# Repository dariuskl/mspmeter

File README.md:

# MSPmeter

This is an ongoing development for a flexible voltage & current meter based on
MSP430i2x, currently in somewhat of a proof-of-concept phase. The goal is to
have a template that can be easily adapted to replace analog or inaccurate
digital panel meters in existing power supplies or to integrate into new
designs. Accuracy-wise it would be nice to achieve .1 mV resp. .1 mA, so that
the readout can be trusted at a resolution of 1 mV resp. 1 mA.

## Planned features

- Buzzer
- Persistent calibration

## User manual

### Digital readout & indicators

### Heartbeat LED

### Buzzer

### Serial interface

9600N1

### Calibration & configuration

# Hardware

## Design notes

### Achievable accuracy

The required accuracy is 1 mV maximum error for the voltage measurement (because
we are aiming for a resolution of 10 mV) and 0.1 mA maximum error for the
current measurement (again, because we are aiming for a resolution of 1 mA).

The internal measurement circuitry of the power supply sources 1 mA for
full-scale voltage and current. To obtain 928 mV max. full-scale ADC input,
a resistor is used to drop a proportional voltage.

    R = 928 mV / 1 mA = 928 Ω

The next closest standard value *below* (we do not want to exceed that voltage)
is 910 Ω. The best readily available performer is `RN73H1JTTD9100A05` with 0.05%
tolerance and 5ppm/°C temperature drift.

That configuration yields below voltage input specification to the ADC.

    0..1 mA / (910 R ± 0.05% ± 5ppm/°C) = 910 mV ± 0.05% ± 5ppm/°C

An operating temperature range of 15 to 60 °C is a reasonable choice for such an
instrument. This yields a worst-case error range of

    0.910 * 0.000005 * (15 - 25) = −0,0000455 (~0,05 mV)
    0.910 * 0.000005 * (60 - 25) =  0,00015925 (~0,16 mV)

The final accuracy specification based on the input circuit over the full
temperature range is thus ~ 5 mV error (in terms of measured output voltage)
and ~ 0.2 mA error (in terms of measured output current).

## I/O

    ──────────────┐
             P1.0 ├─ HEARTBEAT
             P1.1 ├─
     UCA0RXD/P1.2 ├─ Rx
     UCA0TXD/P1.3 ├─ Tx
     UCB0STE/P1.4 ├─ RCLK
     UCB0CLK/P1.5 ├─ SRCLK
       TA0.2/P1.6 ├─ BUZZER
    UCB0SIMO/P1.7 ├─ SER
                  │
             P2.0 ├─ nS1_PRESSED
             P2.1 ├─ ENCODER_A
             P2.2 ├─ ENCODER_B
             P2.3 ├─
    ──────────────┘

## Adjustment procedure

A correctly adjusted unit can achieve accuracy of ???

| Parameter | VCC | Min | Typ | Max | Unit |
|-----------|-----|-----|-----|-----|------|
| VREF      | 3 V | 1.0 | 1.2 | 1.5 | V    |
| ZID       | 3 V | 300 | 400 |     | kΩ   |

The adjustment steps have to performed in the exact order in which they are
given here and no steps may be skipped. There is no way to cancel the adjustment
half-way through.

### Input attenuator trim

If the input attenuator consists of fixed resistors, this step will be skipped.
It is not advisable to use a trimmer due to the associated temperature
coefficient, which is usually much higher than in good fixed resistors.

The input attenuator must be adjusted such that a nominal full-scale input 
yields a voltage of 928 mV on the input pins. In the range of ±928 mV is where
the MSP has the best accuracy (at a gain of 1). Otherwise, the setting is not
critical for accuracy. Just make sure not to exceed 928 mV with the range of
interest. In case of doubt, choose an input voltage in excess of the range.

1. Connect an external voltage source of the nominal full-scale input voltage to
     the input;
2. connect a voltmeter directly to the analog inputs of the MSP; then
3. adjust the trimmer for a reading of 928 mV.

### Voltage reference

To calibrate the voltage reference

1. connect a precise (how precise?) external voltage (what value?) to any (which?) input (how can I measure just the external voltage without the input circuit?);
2. measure the applied input voltage,
3. calculate actual reference voltage from theoretical value
4. check plausibility
5. apply

### Input dividers, impedance, & offset

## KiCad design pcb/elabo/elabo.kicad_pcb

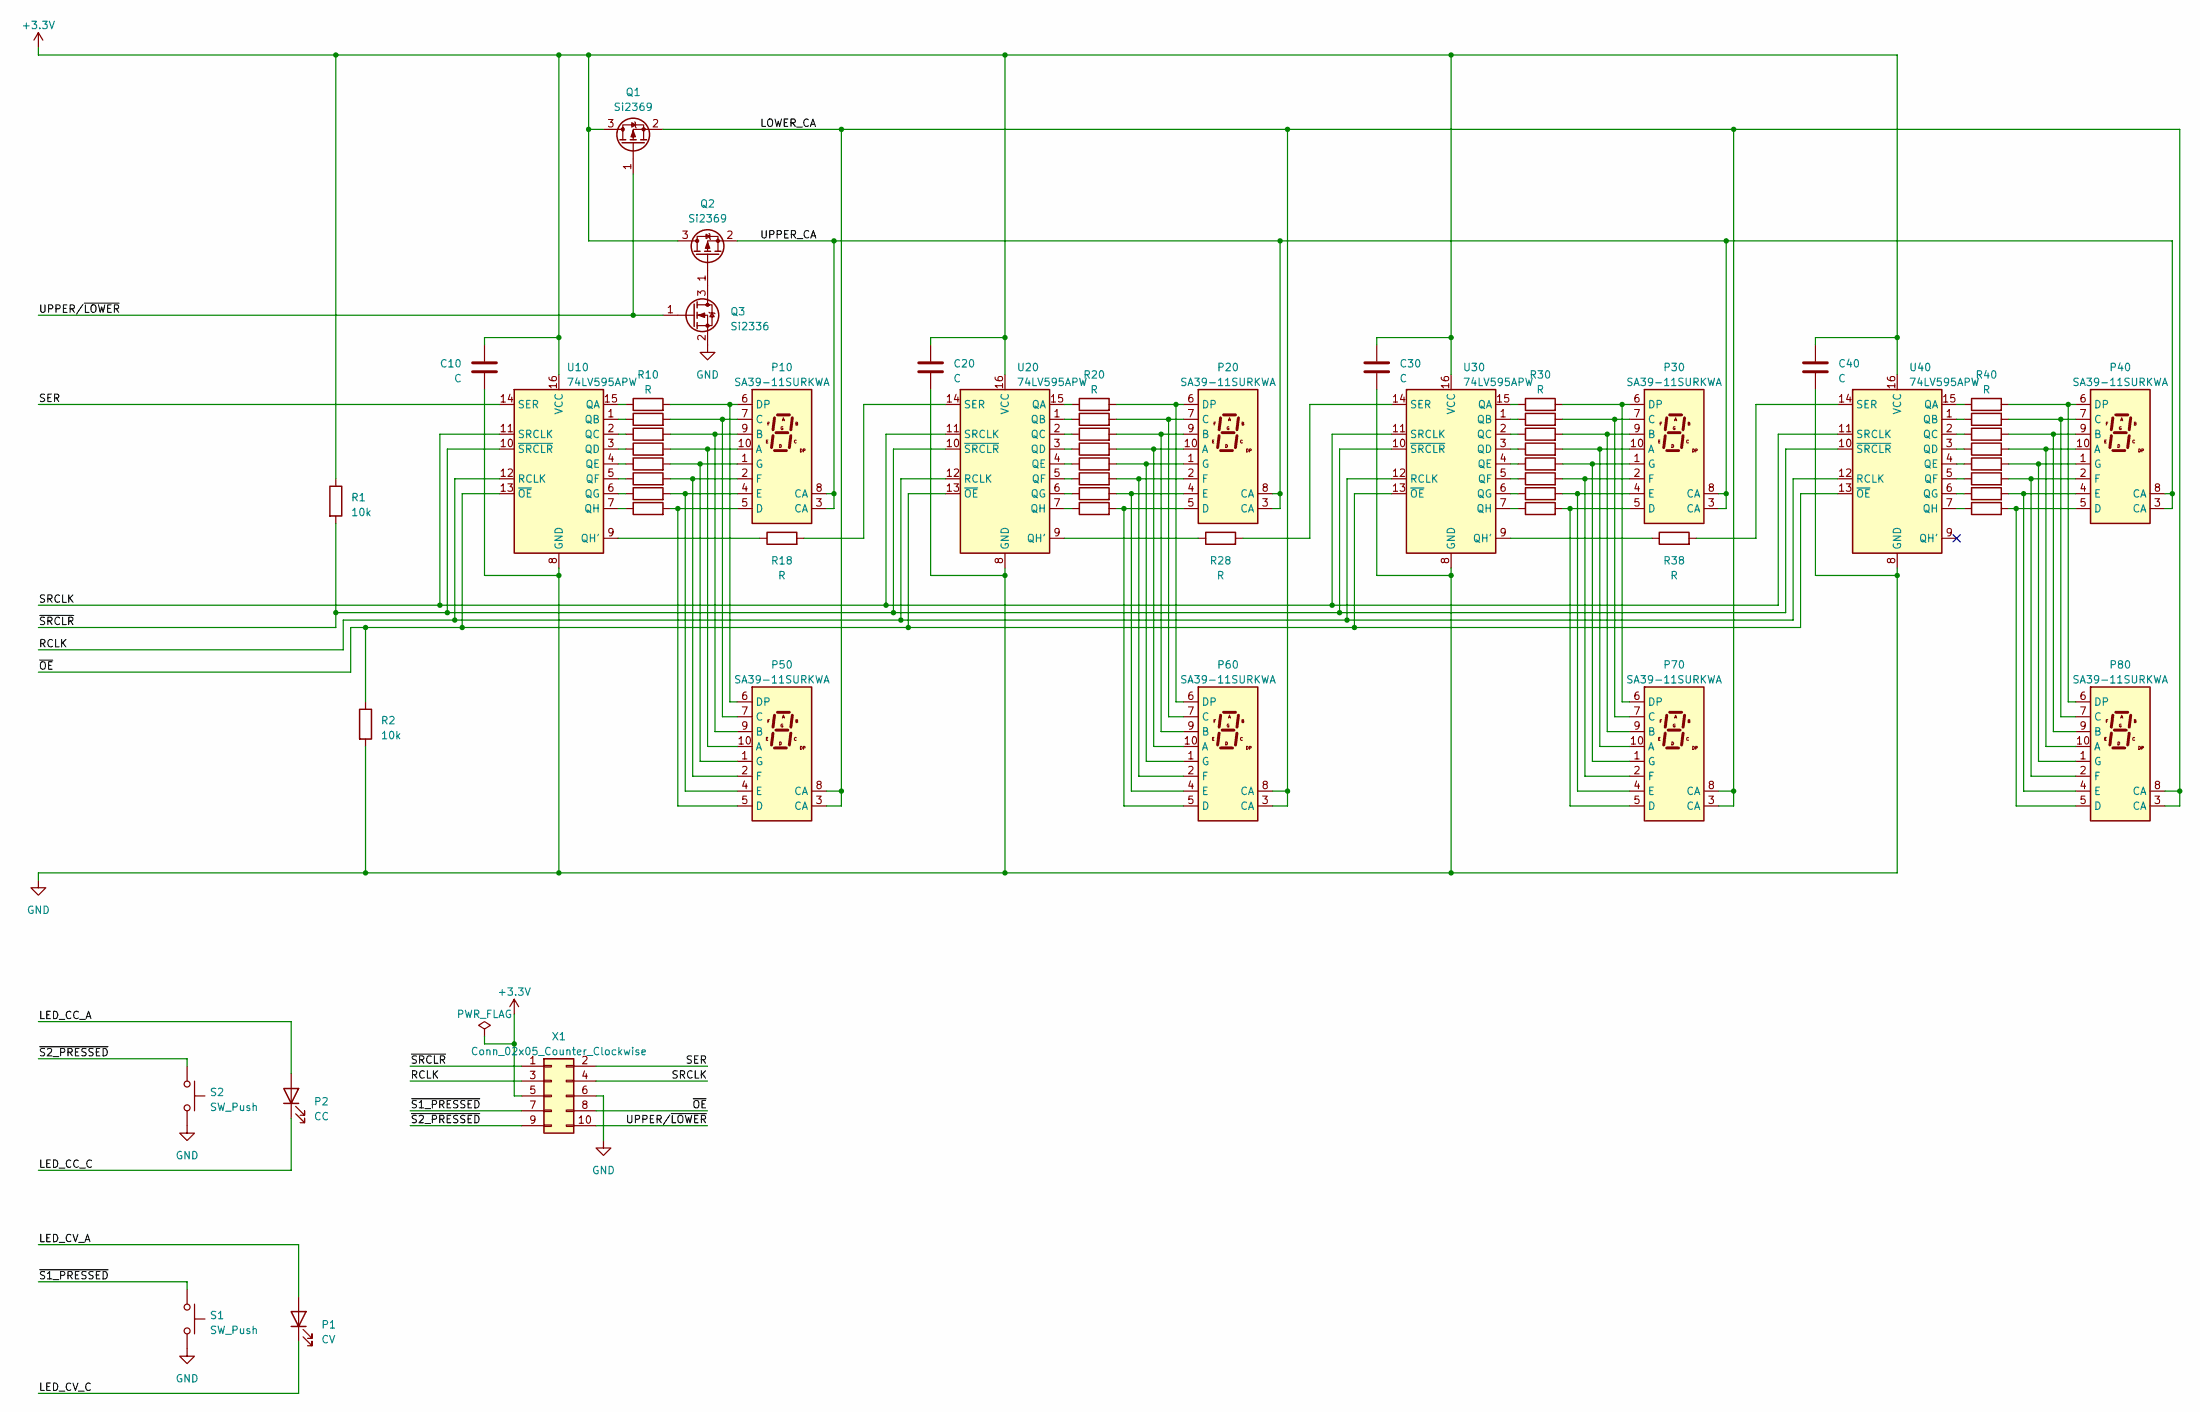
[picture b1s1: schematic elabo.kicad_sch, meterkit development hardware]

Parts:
C10, C20, C30, C40: C; C_0603_1608Metric
P1: CV; LED_D3.0mm_FlatTop
P2: CC; LED_D3.0mm_FlatTop
P10, P20, P30, P40, P50, P60, P70, P80: SA39-11SURKWA; Sx39-1xxxxx
Q1, Q2: Si2369; SOT-23-3
Q3: Si2336; SOT-23-3
R1, R2: 10k; R_0603_1608Metric
R10, R11, R12, R13, R14, R15, R16, R17, R18, R20, R21, R22, R23, R24, R25, R26, R27, R28, R30, R31, R32, R33, R34, R35, R36, R37, R38, R40, R41, R42, R43, R44, R45, R46, R47: R; R_0603_1608Metric
S1, S2: SW_Push; SW_PUSH_6mm_H13mm
U10, U20, U30, U40: 74LV595APW; TSSOP-16_4.4x5mm_P0.65mm
X1: Conn_02x05_Counter_Clockwise; PinHeader_2x05_P2.54mm_Vertical

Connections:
+3.3V: C10.1, C20.1, C30.1, C40.1, Q1.3 (D), Q2.3 (D), R1.1, U10.16 (VCC), U20.16 (VCC), U30.16 (VCC), U40.16 (VCC), X1.5
/LED_CC_A: P2.2 (A)
/LED_CC_C: P2.1 (K)
/LED_CV_A: P1.2 (A)
/LED_CV_C: P1.1 (K)
/LOWER_CA: P50.3 (CA), P50.8 (CA), P60.3 (CA), P60.8 (CA), P70.3 (CA), P70.8 (CA), P80.3 (CA), P80.8 (CA), Q1.2 (S)
/RCLK: U10.12 (RCLK), U20.12 (RCLK), U30.12 (RCLK), U40.12 (RCLK), X1.3
/SER: U10.14 (SER), X1.2
/SRCLK: U10.11 (SRCLK), U20.11 (SRCLK), U30.11 (SRCLK), U40.11 (SRCLK), X1.4
/UPPER_CA: P10.3 (CA), P10.8 (CA), P20.3 (CA), P20.8 (CA), P30.3 (CA), P30.8 (CA), P40.3 (CA), P40.8 (CA), Q2.2 (S)
/UPPER/~LOWER: Q1.1 (G), Q3.1 (G), X1.10
/~OE: R2.1, U10.13 (~OE), U20.13 (~OE), U30.13 (~OE), U40.13 (~OE), X1.8
/~S1_PRESSED: S1.1, X1.7
/~S2_PRESSED: S2.1, X1.9
/~SRCLR: R1.2, U10.10 (~SRCLR), U20.10 (~SRCLR), U30.10 (~SRCLR), U40.10 (~SRCLR), X1.1
GND: C10.2, C20.2, C30.2, C40.2, Q3.2 (S), R2.2, S1.2, S2.2, U10.8 (GND), U20.8 (GND), U30.8 (GND), U40.8 (GND), X1.6
unnamed: P10.10 (A), P50.10 (A), R13.2
unnamed: P10.9 (B), P50.9 (B), R12.2
unnamed: P10.7 (C), P50.7 (C), R11.2
unnamed: P10.5 (D), P50.5 (D), R17.2
unnamed: P10.6 (DP), P50.6 (DP), R10.2
unnamed: P10.4 (E), P50.4 (E), R16.2
unnamed: P10.2 (F), P50.2 (F), R15.2
unnamed: P10.1 (G), P50.1 (G), R14.2
unnamed: P20.10 (A), P60.10 (A), R23.2
unnamed: P20.9 (B), P60.9 (B), R22.2
unnamed: P20.7 (C), P60.7 (C), R21.2
unnamed: P20.5 (D), P60.5 (D), R27.2
unnamed: P20.6 (DP), P60.6 (DP), R20.2
unnamed: P20.4 (E), P60.4 (E), R26.2
unnamed: P20.2 (F), P60.2 (F), R25.2
unnamed: P20.1 (G), P60.1 (G), R24.2
unnamed: P30.10 (A), P70.10 (A), R33.2
unnamed: P30.9 (B), P70.9 (B), R32.2
unnamed: P30.7 (C), P70.7 (C), R31.2
unnamed: P30.5 (D), P70.5 (D), R37.2
unnamed: P30.6 (DP), P70.6 (DP), R30.2
unnamed: P30.4 (E), P70.4 (E), R36.2
unnamed: P30.2 (F), P70.2 (F), R35.2
unnamed: P30.1 (G), P70.1 (G), R34.2
unnamed: P40.10 (A), P80.10 (A), R43.2
unnamed: P40.9 (B), P80.9 (B), R42.2
unnamed: P40.7 (C), P80.7 (C), R41.2
unnamed: P40.5 (D), P80.5 (D), R47.2
unnamed: P40.6 (DP), P80.6 (DP), R40.2
unnamed: P40.4 (E), P80.4 (E), R46.2
unnamed: P40.2 (F), P80.2 (F), R45.2
unnamed: P40.1 (G), P80.1 (G), R44.2
unnamed: Q2.1 (G), Q3.3 (D)
unnamed: R10.1, U10.15 (QA)
unnamed: R11.1, U10.1 (QB)
unnamed: R12.1, U10.2 (QC)
unnamed: R13.1, U10.3 (QD)
unnamed: R14.1, U10.4 (QE)
unnamed: R15.1, U10.5 (QF)
unnamed: R16.1, U10.6 (QG)
unnamed: R18.1, U10.9 (QH')
unnamed: R17.1, U10.7 (QH)
unnamed: R20.1, U20.15 (QA)
unnamed: R21.1, U20.1 (QB)
unnamed: R22.1, U20.2 (QC)
unnamed: R23.1, U20.3 (QD)
unnamed: R24.1, U20.4 (QE)
unnamed: R25.1, U20.5 (QF)
unnamed: R26.1, U20.6 (QG)
unnamed: R28.1, U20.9 (QH')
unnamed: R27.1, U20.7 (QH)
unnamed: R18.2, U20.14 (SER)
unnamed: R30.1, U30.15 (QA)
unnamed: R31.1, U30.1 (QB)
unnamed: R32.1, U30.2 (QC)
unnamed: R33.1, U30.3 (QD)
unnamed: R34.1, U30.4 (QE)
unnamed: R35.1, U30.5 (QF)
unnamed: R36.1, U30.6 (QG)
unnamed: R38.1, U30.9 (QH')
unnamed: R37.1, U30.7 (QH)
unnamed: R28.2, U30.14 (SER)
unnamed: R40.1, U40.15 (QA)
unnamed: R41.1, U40.1 (QB)
unnamed: R42.1, U40.2 (QC)
unnamed: R43.1, U40.3 (QD)
unnamed: R44.1, U40.4 (QE)
unnamed: R45.1, U40.5 (QF)
unnamed: R46.1, U40.6 (QG)
unnamed: R47.1, U40.7 (QH)
unnamed: R38.2, U40.14 (SER)

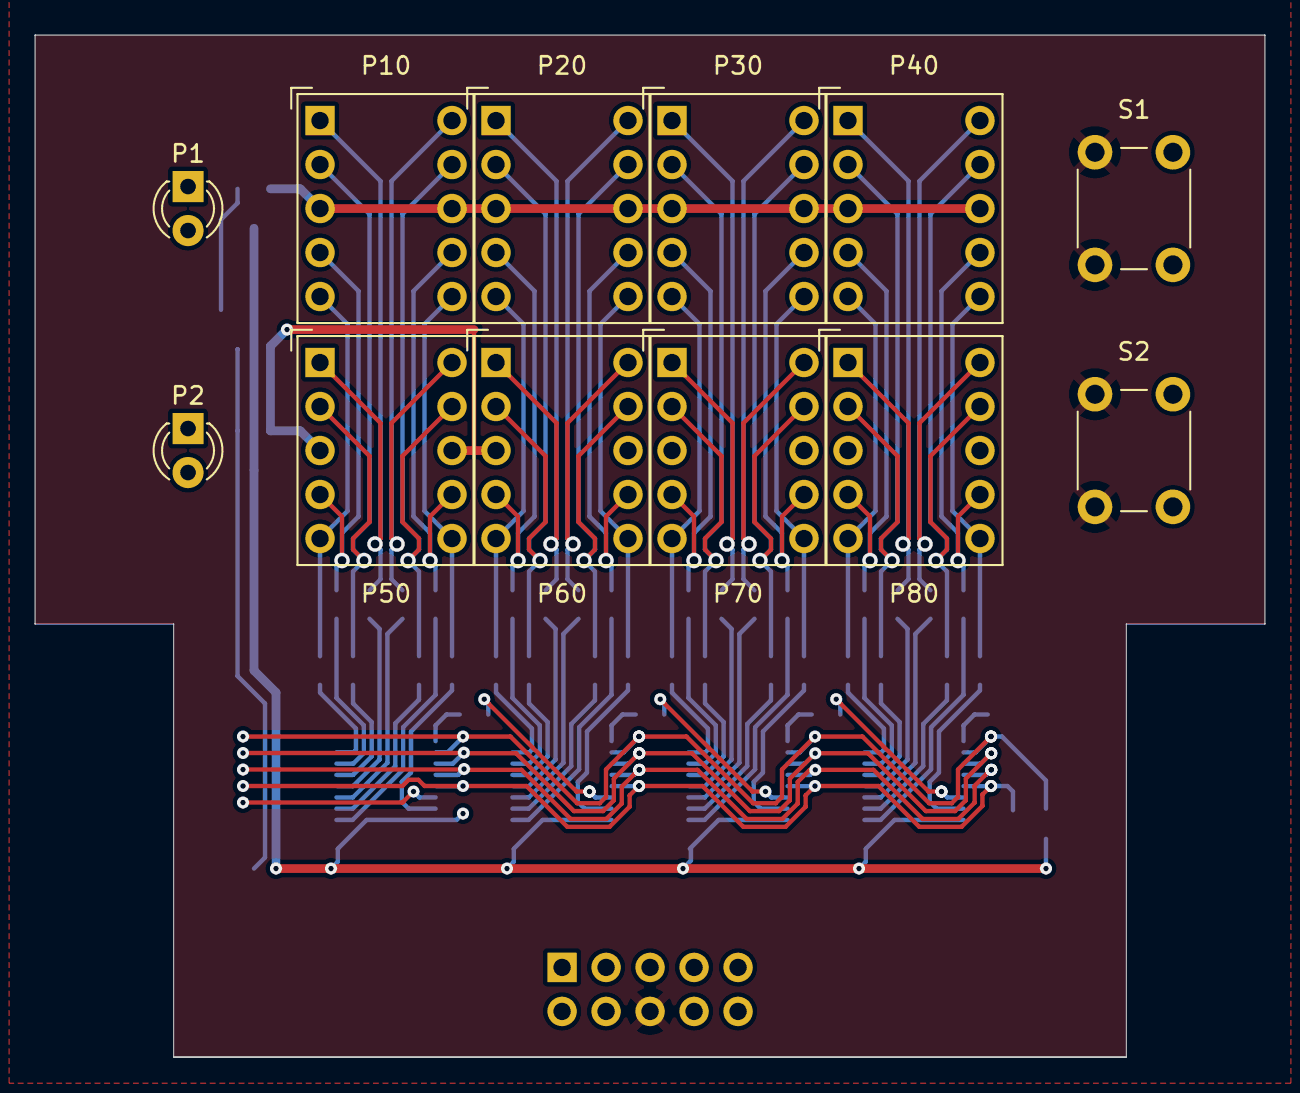
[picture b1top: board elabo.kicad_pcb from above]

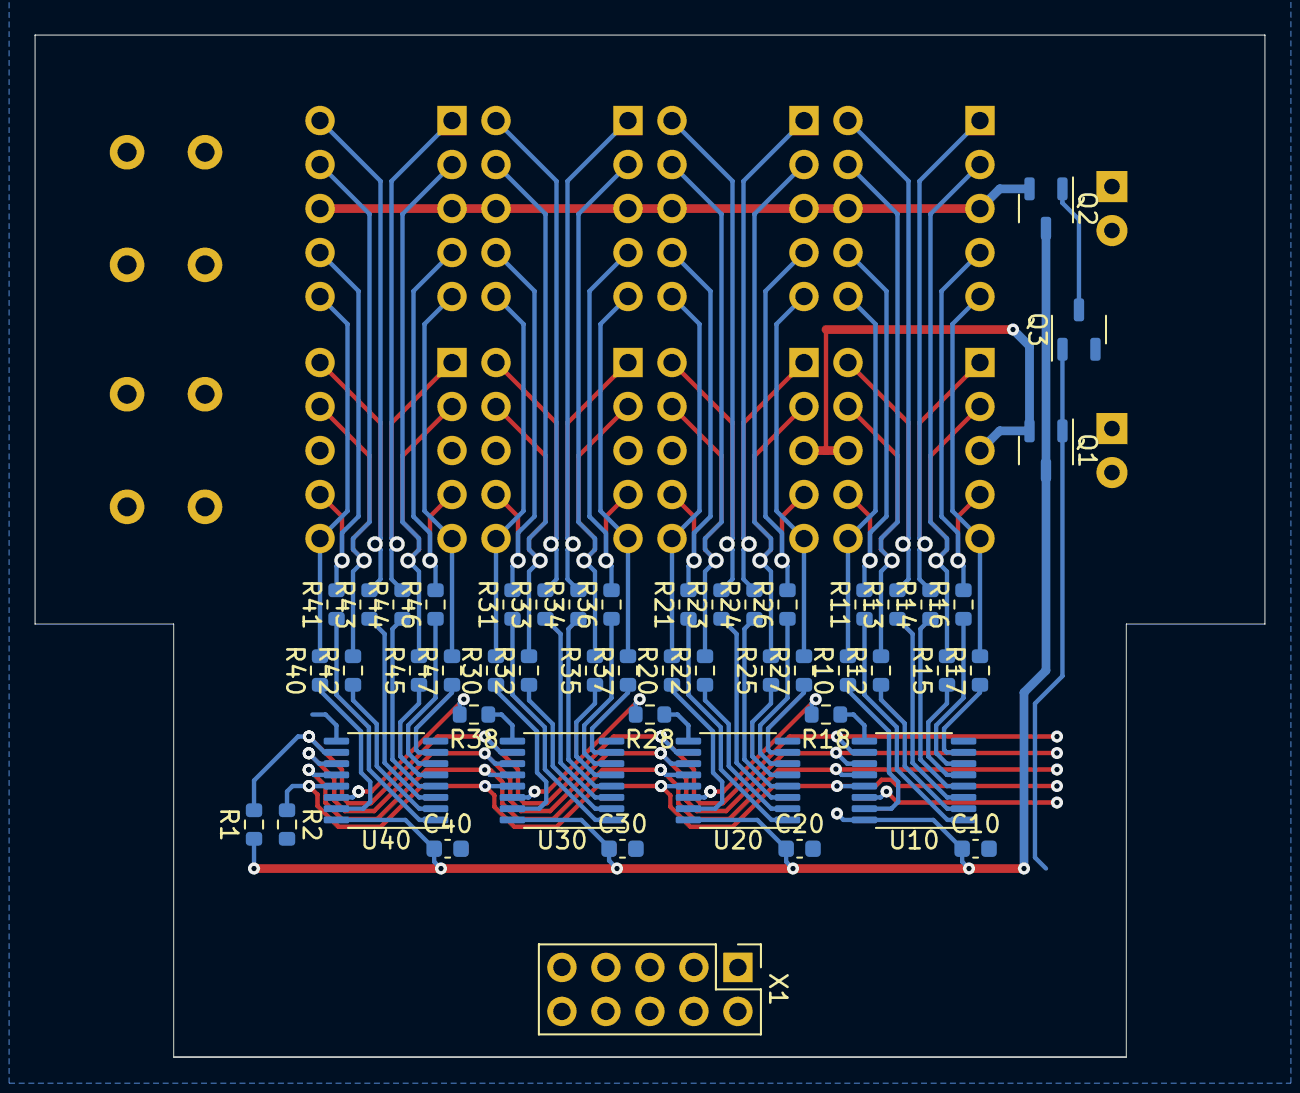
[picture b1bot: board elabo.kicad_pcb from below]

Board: 2 copper layers, 71.0 x 59.0 mm, 61 parts (49 on the bottom side), 83 nets.

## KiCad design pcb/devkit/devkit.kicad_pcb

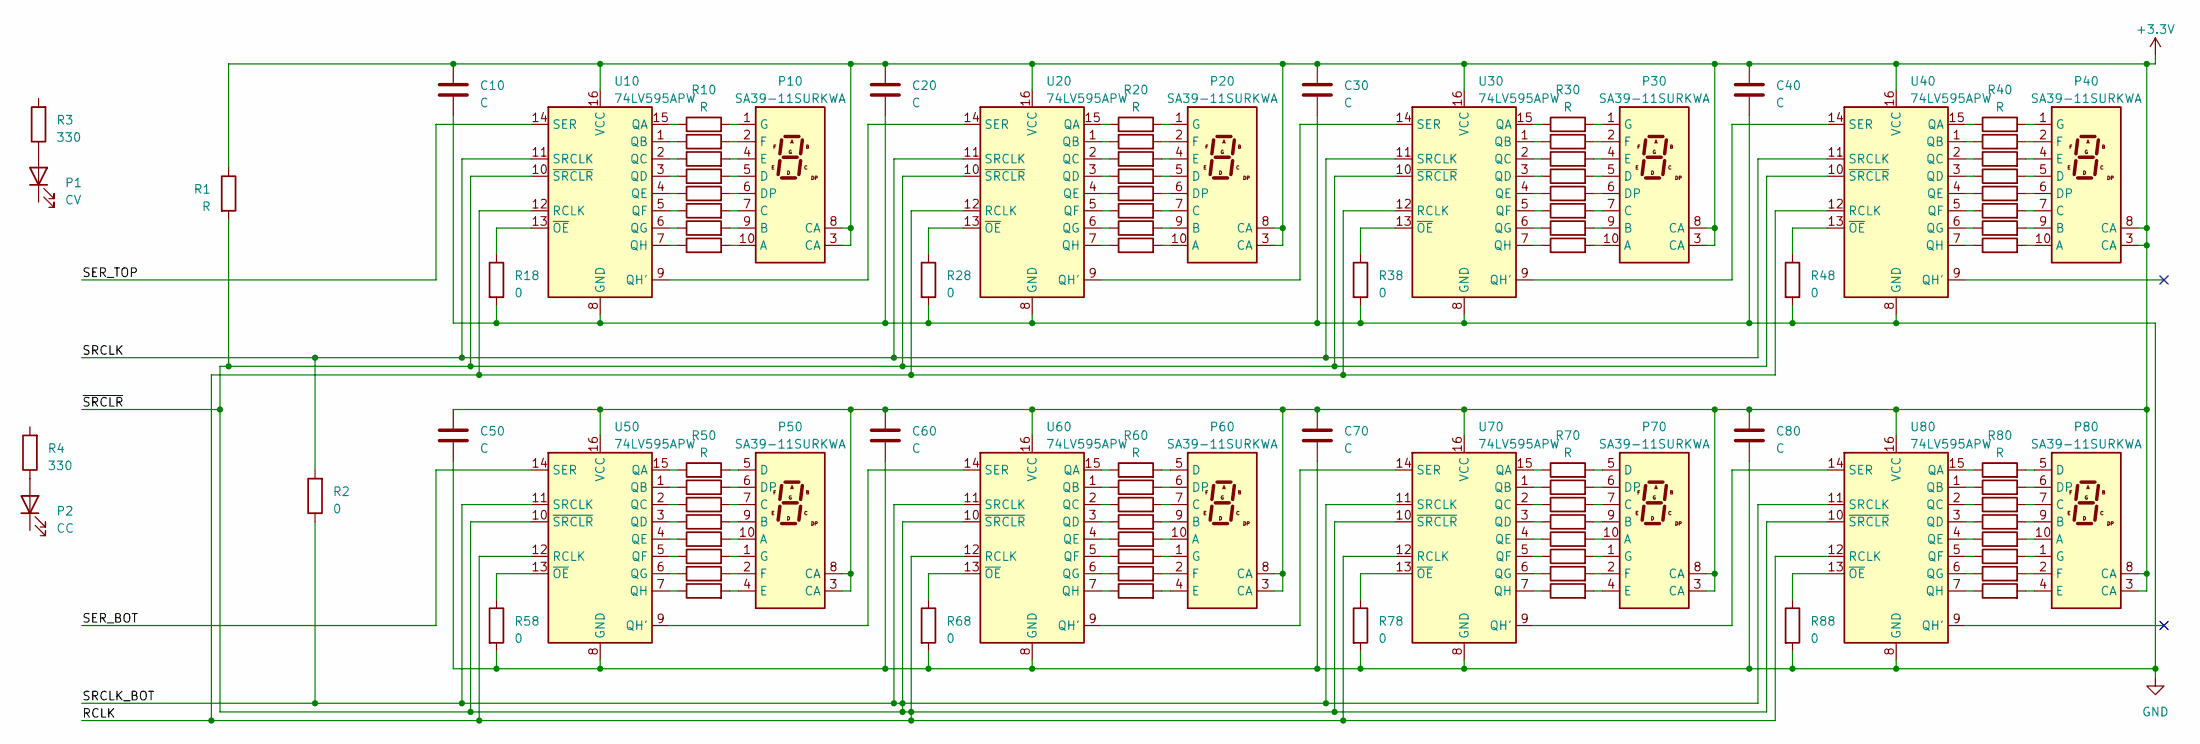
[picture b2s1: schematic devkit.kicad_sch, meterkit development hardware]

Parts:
C10, C20, C30, C40, C50, C60, C70, C80: C; C_0603_1608Metric
P1: CV; LED_D3.0mm_FlatTop
P2: CC; LED_D3.0mm_FlatTop
P10, P20, P30, P40, P50, P60, P70, P80: SA39-11SURKWA; Sx39-1xxxxx
R1, R10, R11, R12, R13, R14, R15, R16, R17, R20, R21, R22, R23, R24, R25, R26, R27, R30, R31, R32, R33, R34, R35, R36, R37, R40, R41, R42, R43, R44, R45, R46, R47, R50, R51, R52, R53, R54, R55, R56, R57, R60, R61, R62, R63, R64, R65, R66, R67, R70, R71, R72, R73, R74, R75, R76, R77, R80, R81, R82, R83, R84, R85, R86, R87: R; R_0603_1608Metric
R2, R18, R28, R38, R48, R58, R68, R78, R88: 0; R_0603_1608Metric
R3, R4: 330; R_0603_1608Metric
U10, U20, U30, U40, U50, U60, U70, U80: 74LV595APW; TSSOP-16_4.4x5mm_P0.65mm

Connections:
+3.3V: C10.1, C20.1, C30.1, C40.1, C50.1, C60.1, C70.1, C80.1, P10.3 (CA), P10.8 (CA), P20.3 (CA), P20.8 (CA), P30.3 (CA), P30.8 (CA), P40.3 (CA), P40.8 (CA), P50.3 (CA), P50.8 (CA), P60.3 (CA), P60.8 (CA), P70.3 (CA), P70.8 (CA), P80.3 (CA), P80.8 (CA), R1.1, U10.16 (VCC), U20.16 (VCC), U30.16 (VCC), U40.16 (VCC), U50.16 (VCC), U60.16 (VCC), U70.16 (VCC), U80.16 (VCC)
/RCLK: R1.2, R2.1, U10.10 (~SRCLR), U10.12 (RCLK), U20.10 (~SRCLR), U20.12 (RCLK), U30.10 (~SRCLR), U30.12 (RCLK), U40.10 (~SRCLR), U40.12 (RCLK), U50.10 (~SRCLR), U50.11 (SRCLK), U50.12 (RCLK), U60.10 (~SRCLR), U60.11 (SRCLK), U60.12 (RCLK), U70.10 (~SRCLR), U70.11 (SRCLK), U70.12 (RCLK), U80.10 (~SRCLR), U80.11 (SRCLK), U80.12 (RCLK)
/SER_BOT: U50.14 (SER)
/SER_TOP: U10.14 (SER)
/SRCLK: R2.2, U10.11 (SRCLK), U20.11 (SRCLK), U30.11 (SRCLK), U40.11 (SRCLK)
GND: C10.2, C20.2, C30.2, C40.2, C50.2, C60.2, C70.2, C80.2, R18.2, R28.2, R38.2, R48.2, R58.2, R68.2, R78.2, R88.2, U10.8 (GND), U20.8 (GND), U30.8 (GND), U40.8 (GND), U50.8 (GND), U60.8 (GND), U70.8 (GND), U80.8 (GND)
unnamed: P1.2 (A), R3.1
unnamed: P2.2 (A), R4.1
unnamed: P10.10 (A), R17.2
unnamed: P10.9 (B), R16.2
unnamed: P10.7 (C), R15.2
unnamed: P10.5 (D), R13.2
unnamed: P10.6 (DP), R14.2
unnamed: P10.4 (E), R12.2
unnamed: P10.2 (F), R11.2
unnamed: P10.1 (G), R10.2
unnamed: P20.10 (A), R27.2
unnamed: P20.9 (B), R26.2
unnamed: P20.7 (C), R25.2
unnamed: P20.5 (D), R23.2
unnamed: P20.6 (DP), R24.2
unnamed: P20.4 (E), R22.2
unnamed: P20.2 (F), R21.2
unnamed: P20.1 (G), R20.2
unnamed: P30.10 (A), R37.2
unnamed: P30.9 (B), R36.2
unnamed: P30.7 (C), R35.2
unnamed: P30.5 (D), R33.2
unnamed: P30.6 (DP), R34.2
unnamed: P30.4 (E), R32.2
unnamed: P30.2 (F), R31.2
unnamed: P30.1 (G), R30.2
unnamed: P40.10 (A), R47.2
unnamed: P40.9 (B), R46.2
unnamed: P40.7 (C), R45.2
unnamed: P40.5 (D), R43.2
unnamed: P40.6 (DP), R44.2
unnamed: P40.4 (E), R42.2
unnamed: P40.2 (F), R41.2
unnamed: P40.1 (G), R40.2
unnamed: P50.10 (A), R54.2
unnamed: P50.9 (B), R53.2
unnamed: P50.7 (C), R52.2
unnamed: P50.5 (D), R50.2
unnamed: P50.6 (DP), R51.2
unnamed: P50.4 (E), R57.2
unnamed: P50.2 (F), R56.2
unnamed: P50.1 (G), R55.2
unnamed: P60.10 (A), R64.2
unnamed: P60.9 (B), R63.2
unnamed: P60.7 (C), R62.2
unnamed: P60.5 (D), R60.2
unnamed: P60.6 (DP), R61.2
unnamed: P60.4 (E), R67.2
unnamed: P60.2 (F), R66.2
unnamed: P60.1 (G), R65.2
unnamed: P70.10 (A), R74.2
unnamed: P70.9 (B), R73.2
unnamed: P70.7 (C), R72.2
unnamed: P70.5 (D), R70.2
unnamed: P70.6 (DP), R71.2
unnamed: P70.4 (E), R77.2
unnamed: P70.2 (F), R76.2
unnamed: P70.1 (G), R75.2
unnamed: P80.10 (A), R84.2
unnamed: P80.9 (B), R83.2
unnamed: P80.7 (C), R82.2
unnamed: P80.5 (D), R80.2
unnamed: P80.6 (DP), R81.2
unnamed: P80.4 (E), R87.2
unnamed: P80.2 (F), R86.2
unnamed: P80.1 (G), R85.2
unnamed: R10.1, U10.15 (QA)
unnamed: R11.1, U10.1 (QB)
unnamed: R12.1, U10.2 (QC)
unnamed: R13.1, U10.3 (QD)
unnamed: R14.1, U10.4 (QE)
unnamed: R15.1, U10.5 (QF)
unnamed: R16.1, U10.6 (QG)
unnamed: U10.9 (QH'), U20.14 (SER)
unnamed: R17.1, U10.7 (QH)
unnamed: R18.1, U10.13 (~OE)
unnamed: R20.1, U20.15 (QA)
unnamed: R21.1, U20.1 (QB)
unnamed: R22.1, U20.2 (QC)
unnamed: R23.1, U20.3 (QD)
unnamed: R24.1, U20.4 (QE)
unnamed: R25.1, U20.5 (QF)
unnamed: R26.1, U20.6 (QG)
unnamed: U20.9 (QH'), U30.14 (SER)
unnamed: R27.1, U20.7 (QH)
unnamed: R28.1, U20.13 (~OE)
unnamed: R30.1, U30.15 (QA)
unnamed: R31.1, U30.1 (QB)
unnamed: R32.1, U30.2 (QC)
unnamed: R33.1, U30.3 (QD)
unnamed: R34.1, U30.4 (QE)
unnamed: R35.1, U30.5 (QF)
unnamed: R36.1, U30.6 (QG)
unnamed: U30.9 (QH'), U40.14 (SER)
unnamed: R37.1, U30.7 (QH)
unnamed: R38.1, U30.13 (~OE)
unnamed: R40.1, U40.15 (QA)
unnamed: R41.1, U40.1 (QB)
unnamed: R42.1, U40.2 (QC)
unnamed: R43.1, U40.3 (QD)
unnamed: R44.1, U40.4 (QE)
unnamed: R45.1, U40.5 (QF)
unnamed: R46.1, U40.6 (QG)
unnamed: R47.1, U40.7 (QH)
unnamed: R48.1, U40.13 (~OE)
unnamed: R50.1, U50.15 (QA)
unnamed: R51.1, U50.1 (QB)
unnamed: R52.1, U50.2 (QC)
unnamed: R53.1, U50.3 (QD)
unnamed: R54.1, U50.4 (QE)
unnamed: R55.1, U50.5 (QF)
unnamed: R56.1, U50.6 (QG)
unnamed: U50.9 (QH'), U60.14 (SER)
unnamed: R57.1, U50.7 (QH)
unnamed: R58.1, U50.13 (~OE)
unnamed: R60.1, U60.15 (QA)
unnamed: R61.1, U60.1 (QB)
unnamed: R62.1, U60.2 (QC)
unnamed: R63.1, U60.3 (QD)
unnamed: R64.1, U60.4 (QE)
unnamed: R65.1, U60.5 (QF)
unnamed: R66.1, U60.6 (QG)
unnamed: U60.9 (QH'), U70.14 (SER)
unnamed: R67.1, U60.7 (QH)
unnamed: R68.1, U60.13 (~OE)
unnamed: R70.1, U70.15 (QA)
unnamed: R71.1, U70.1 (QB)
unnamed: R72.1, U70.2 (QC)
unnamed: R73.1, U70.3 (QD)
unnamed: R74.1, U70.4 (QE)
unnamed: R75.1, U70.5 (QF)
unnamed: R76.1, U70.6 (QG)
unnamed: U70.9 (QH'), U80.14 (SER)
unnamed: R77.1, U70.7 (QH)
unnamed: R78.1, U70.13 (~OE)
unnamed: R80.1, U80.15 (QA)
unnamed: R81.1, U80.1 (QB)
unnamed: R82.1, U80.2 (QC)
unnamed: R83.1, U80.3 (QD)
unnamed: R84.1, U80.4 (QE)
unnamed: R85.1, U80.5 (QF)
unnamed: R86.1, U80.6 (QG)
unnamed: R87.1, U80.7 (QH)
unnamed: R88.1, U80.13 (~OE)

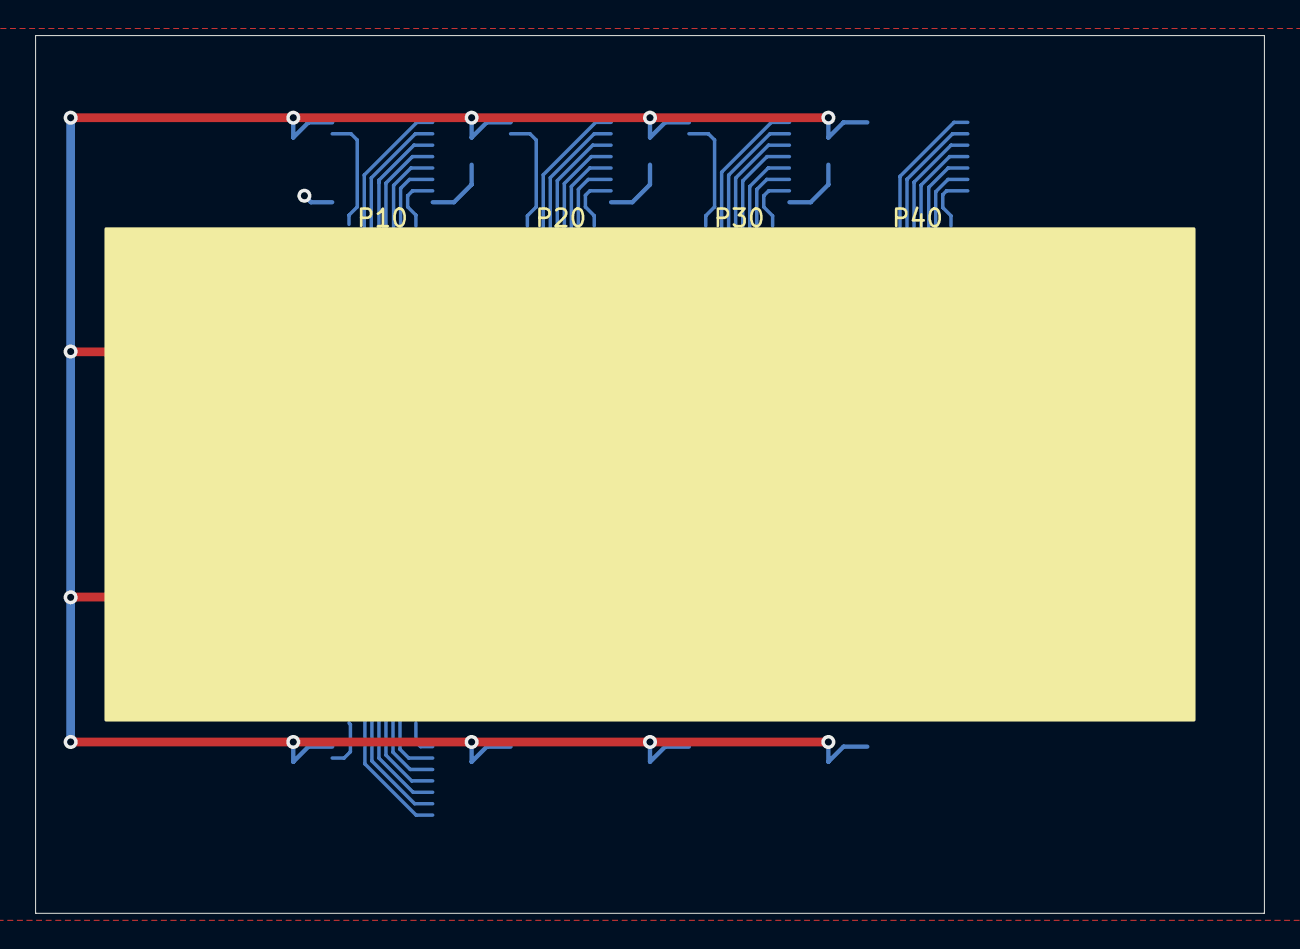
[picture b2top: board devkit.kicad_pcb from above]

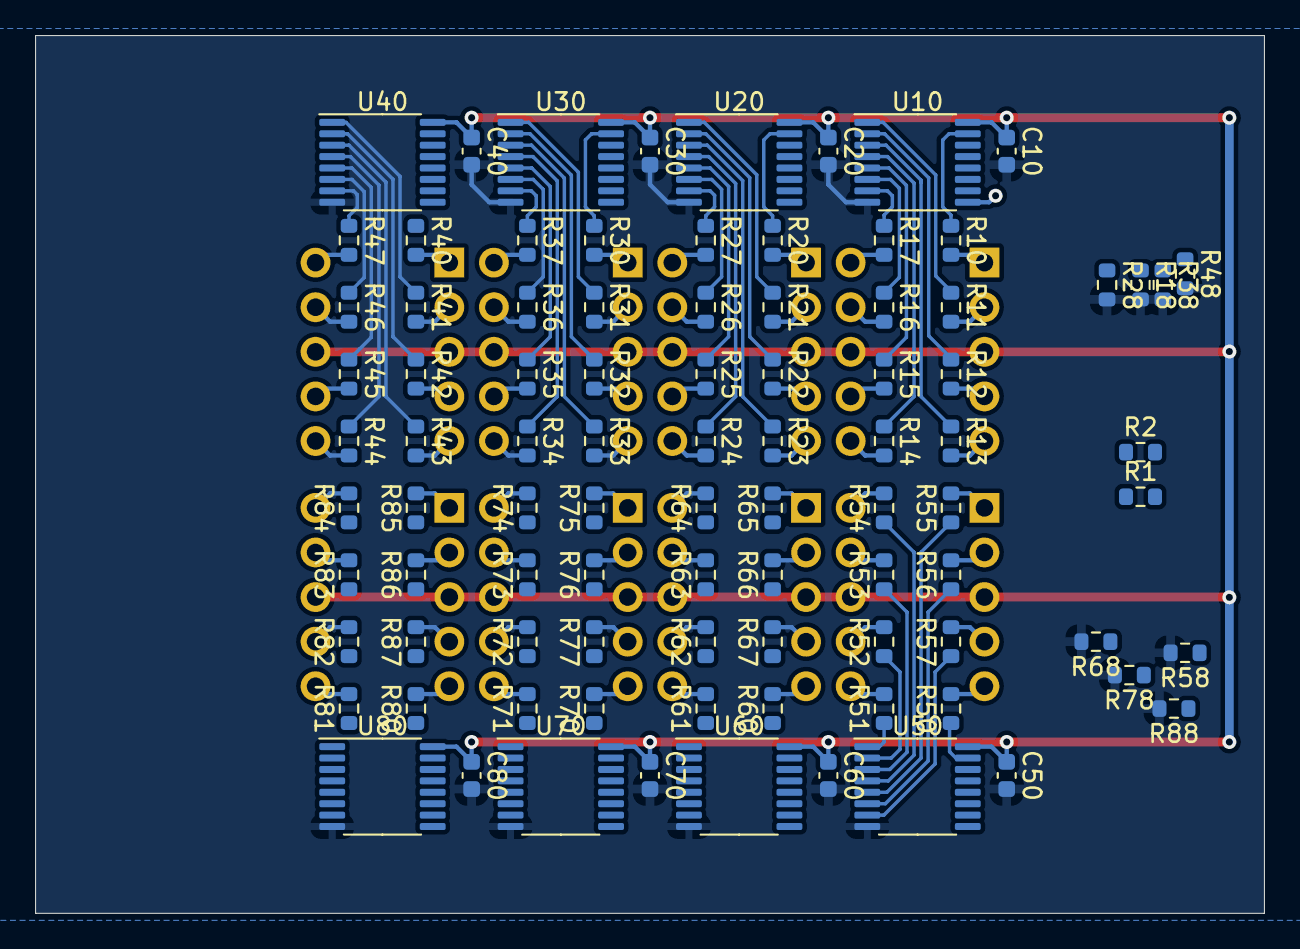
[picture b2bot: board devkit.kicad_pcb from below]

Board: 2 copper layers, 70.0 x 50.0 mm, 98 parts (90 on the bottom side), 146 nets.

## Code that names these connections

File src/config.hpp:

// Meter Firmware / Darius Kellermann <kellermann@proton.me>

#ifndef MSPMETER_CONFIG_HPP
#define MSPMETER_CONFIG_HPP

#include "calibration.hpp"
#include "msp430i2.hpp"

namespace meter {

  constexpr auto used_channels = 4;

  /// The number of samples, which are accumulated in the background and
  /// averaged to obtain one "reading" that is displayed to the user.
  constexpr auto number_of_oversamples = 256;

  constexpr auto default_calibration =
      Array<Channel_calibration, used_channels>{
          {{5'000'000, 30'000'000, msp430i2::SD24::full_scale, 0},
           {1'000'000, 1'000'000, msp430i2::SD24::full_scale, 0},
           {5'000'000, 30'000'000, msp430i2::SD24::full_scale, 0},
           {1'000'000, 1'000'000, msp430i2::SD24::full_scale, 0}}};

  constexpr auto heartbeat_pin = msp430i2::PA::P1_0;
  constexpr auto rx_pin = msp430i2::PA::P1_2;
  constexpr auto tx_pin = msp430i2::PA::P1_3;
  constexpr auto rclk_pin = msp430i2::PA::P1_4;
  constexpr auto srclk_pin = msp430i2::PA::P1_5;
  constexpr auto buzzer_pin = msp430i2::PA::P1_6;
  constexpr auto ser_pin = msp430i2::PA::P1_7;
  constexpr auto ns1_pressed_pin = msp430i2::PA::P2_0;
  constexpr auto encoder_a_pin = msp430i2::PA::P2_1;
  constexpr auto encoder_b_pin = msp430i2::PA::P2_2;

} // namespace meter

#endif // MSPMETER_CONFIG_HPP

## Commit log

2023-07-06 basic functionality present; validation pending
2023-07-06 implemented gain calibration
    This also reduces the computational effort by incorporating the conversion
    from ADC result to voltage into the calibration.
2023-07-10 calibration can be stored to flash now
2023-07-12 measure all used channels
2023-07-12 fix digital outputs
    The default direction of the PADIR register is input.
2023-07-12 better support for build-time configuration of channels
2023-07-12 only measure when readout is not updated
    This could theoretically improve noise performance.
2023-08-08 split 7-segment stuff into separate files
2023-08-08 improve calibration and use all available channels
2023-08-08 format_readout() takes a slice now for increased flexibility
